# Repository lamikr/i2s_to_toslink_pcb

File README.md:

I2S to Toslink PCB

Kicad 7.0 schematic and PCB project for PCB that
can generate optical AES/EBU signal for Toslink audio adapter. PCB uses the
WM8805 chipset as a codec for transforming the signal from I2S to AES/EBU Toslink.

PCB has following input pins:
- 5V power
- GND
- I2S data
- I2S LRCLK
- I2S BCLK
- I2S MCLK (optional)

PCB can either be configured to use the external MCLK or generate the MCLK from the BCLK.
Generation of MCLK is usually needed because the WM8805 does not always work with the external
MCLK and that is hearable as a small errors and cracks on audio.

Project will also need the firmware for ATmega chip so that it can configure the PLL generator
and WM8805 over I2C lines to right mode.

By default the WM8805 codec GPO0 and GPO7 are pulled down so that the WM8805 is configured to use 16 bit I2S data.
But those gpio's can be pulled also to UP to 3V3 voltage to configure the WM8805 to handle 24 bit I2S data if needed.
(see wm8805 docs for details). Codec can also be resetted externally via reset pin. (ATmega has free gpios with headers to drive those pins if you want to add the jumper wires and modify firmware)

[Schematics in PDF document](./docs/schematics/schematics.pdf)

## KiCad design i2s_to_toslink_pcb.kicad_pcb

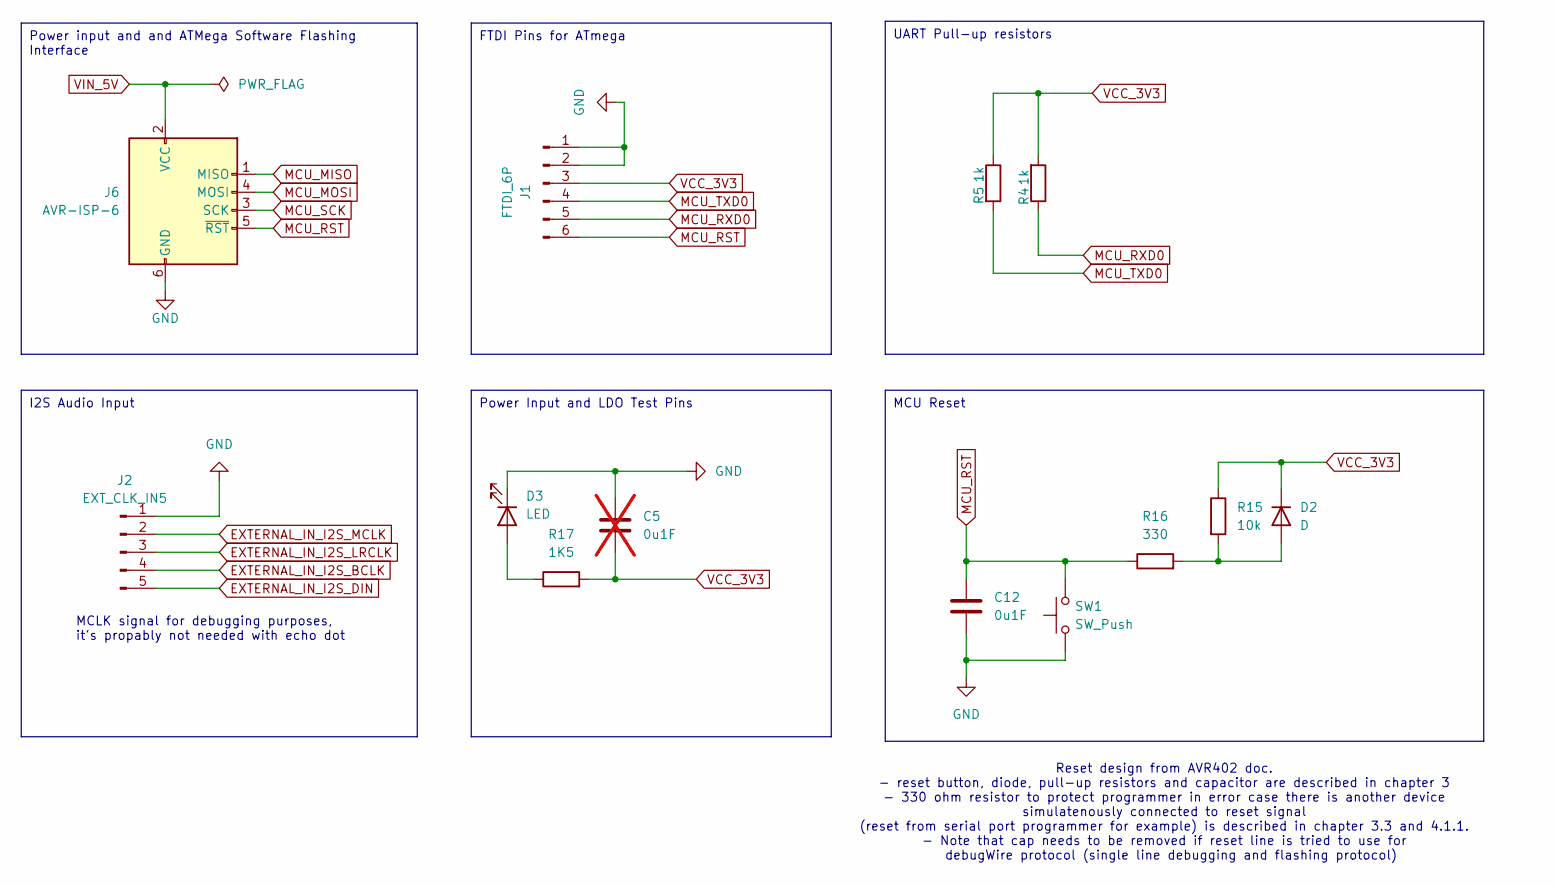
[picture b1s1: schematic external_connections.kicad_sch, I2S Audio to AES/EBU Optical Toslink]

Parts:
C5: 0u1F; C_0603_1608Metric; MPN GRM033R61A104ME15D; not fitted
C12: 0u1F; C_0603_1608Metric
D2: D; D_0603_1608Metric
D3: LED; LED_0805_2012Metric; MPN QBLP631-AG
J1: FTDI_6P; PinHeader_1x06_P2.54mm_Vertical; MPN 10129378-920001BLF-ND
J2: EXT_CLK_IN5; PinHeader_1x05_P2.54mm_Vertical
J6: AVR-ISP-6; PinHeader_2x03_P2.54mm_Vertical; MPN 75869-131LF
R4: 1k; R_0603_1608Metric; MPN RC0402FR-0710KL
R5: 1k; R_0603_1608Metric; MPN RC0402FR-070RL
R15: 10k; R_0603_1608Metric
R16: 330; R_0603_1608Metric
R17: 1K5; R_0603_1608Metric; MPN RC0402FR-071K5L
SW1: SW_Push; SW_SPST_B3U-1000P

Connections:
EXTERNAL_IN_I2S_BCLK: J2.4; also elsewhere on the board
EXTERNAL_IN_I2S_DIN: J2.5; also elsewhere on the board
EXTERNAL_IN_I2S_LRCLK: J2.3; also elsewhere on the board
EXTERNAL_IN_I2S_MCLK: J2.2; also elsewhere on the board
GND: C5.1, C12.2, D3.1 (K), J1.1, J1.2, J2.1, J6.6 (GND), SW1.1; also elsewhere on the board
MCU_MISO: J6.1 (MISO); also elsewhere on the board
MCU_MOSI: J6.4 (MOSI); also elsewhere on the board
MCU_RST: C12.1, J1.6, J6.5 (~RST), R16.1, SW1.2; also elsewhere on the board
MCU_RXD0: J1.5, R4.1; also elsewhere on the board
MCU_SCK: J6.3 (SCK); also elsewhere on the board
MCU_TXD0: J1.4, R5.2; also elsewhere on the board
unnamed: D2.2 (A), R15.2, R16.2
unnamed: D3.2 (A), R17.1
VCC_3V3: C5.2, D2.1 (K), J1.3, R4.2, R5.1, R15.1, R17.2; also elsewhere on the board
VIN_5V: J6.2 (VCC); also elsewhere on the board

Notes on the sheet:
Power input and and ATMega Software Flashing Interface
MCU Reset
UART Pull-up resistors
FTDI Pins for ATmega
I2S Audio Input
Power Input and LDO Test Pins
MCLK signal for debugging purposes, it's propably not needed with echo dot
Reset design from AVR402 doc. - reset button, diode, pull-up resistors and capacitor are described in chapter 3 - 330 ohm resistor to protect programmer in error case there is another device simulatenously connected to reset signal (reset from serial port programmer for example) is described in cha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

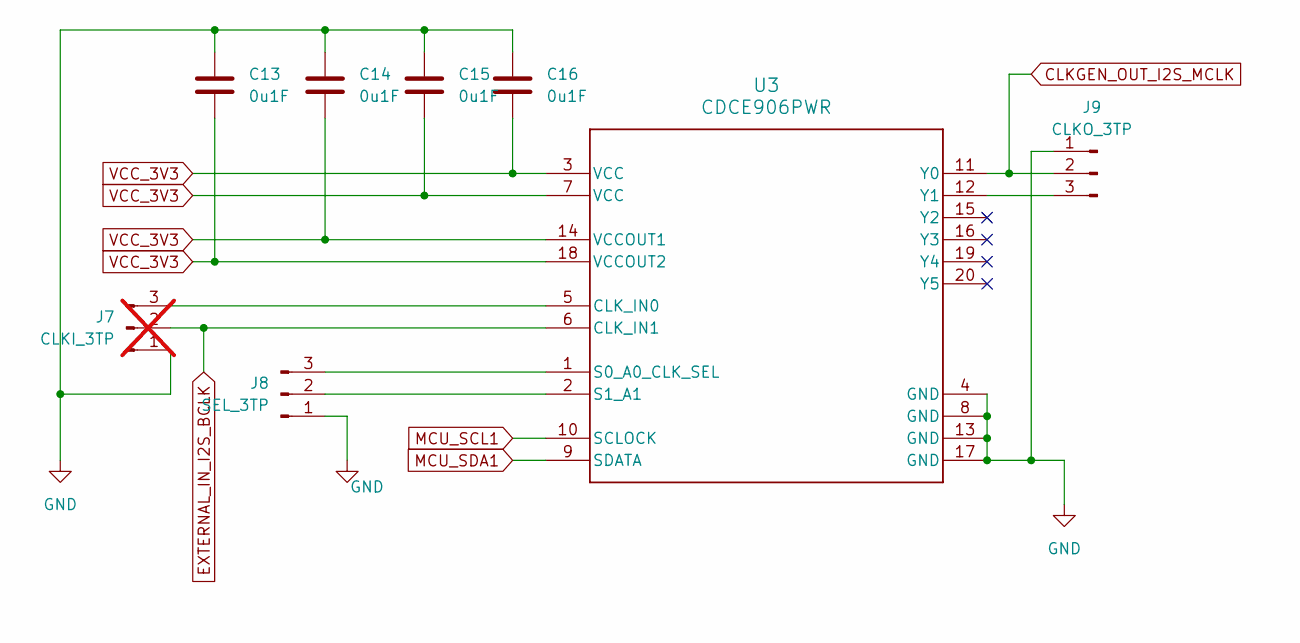
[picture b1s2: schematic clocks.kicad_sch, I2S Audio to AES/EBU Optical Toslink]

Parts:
C13, C14, C15, C16: 0u1F; C_0603_1608Metric; MPN GRM033R61A104ME15D
J7: CLKI_3TP; PinHeader_1x03_P2.54mm_Vertical; not fitted
J8: SEL_3TP; PinHeader_1x03_P2.54mm_Vertical
J9: CLKO_3TP; PinHeader_1x03_P2.54mm_Vertical
U3: CDCE906PWR; PW0020A-IPC_A; MPN CDCE906PWR

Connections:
CLKGEN_OUT_I2S_MCLK: J9.2, U3.11 (Y0); also elsewhere on the board
EXTERNAL_IN_I2S_BCLK: J7.2, U3.6 (CLK_IN1); also elsewhere on the board
GND: C13.1, C14.1, C15.1, C16.1, J7.1, J8.1, J9.1, U3.4 (GND), U3.8 (GND), U3.13 (GND), U3.17 (GND); also elsewhere on the board
MCU_SCL1: U3.10 (SCLOCK); also elsewhere on the board
MCU_SDA1: U3.9 (SDATA); also elsewhere on the board
unnamed: J7.3, U3.5 (CLK_IN0)
unnamed: J8.2, U3.2 (S1_A1)
unnamed: J8.3, U3.1 (S0_A0_CLK_SEL)
unnamed: J9.3, U3.12 (Y1)
VCC_3V3: C13.2, C14.2, C15.2, C16.2, U3.3 (VCC), U3.7 (VCC), U3.14 (VCCOUT1), U3.18 (VCCOUT2); also elsewhere on the board

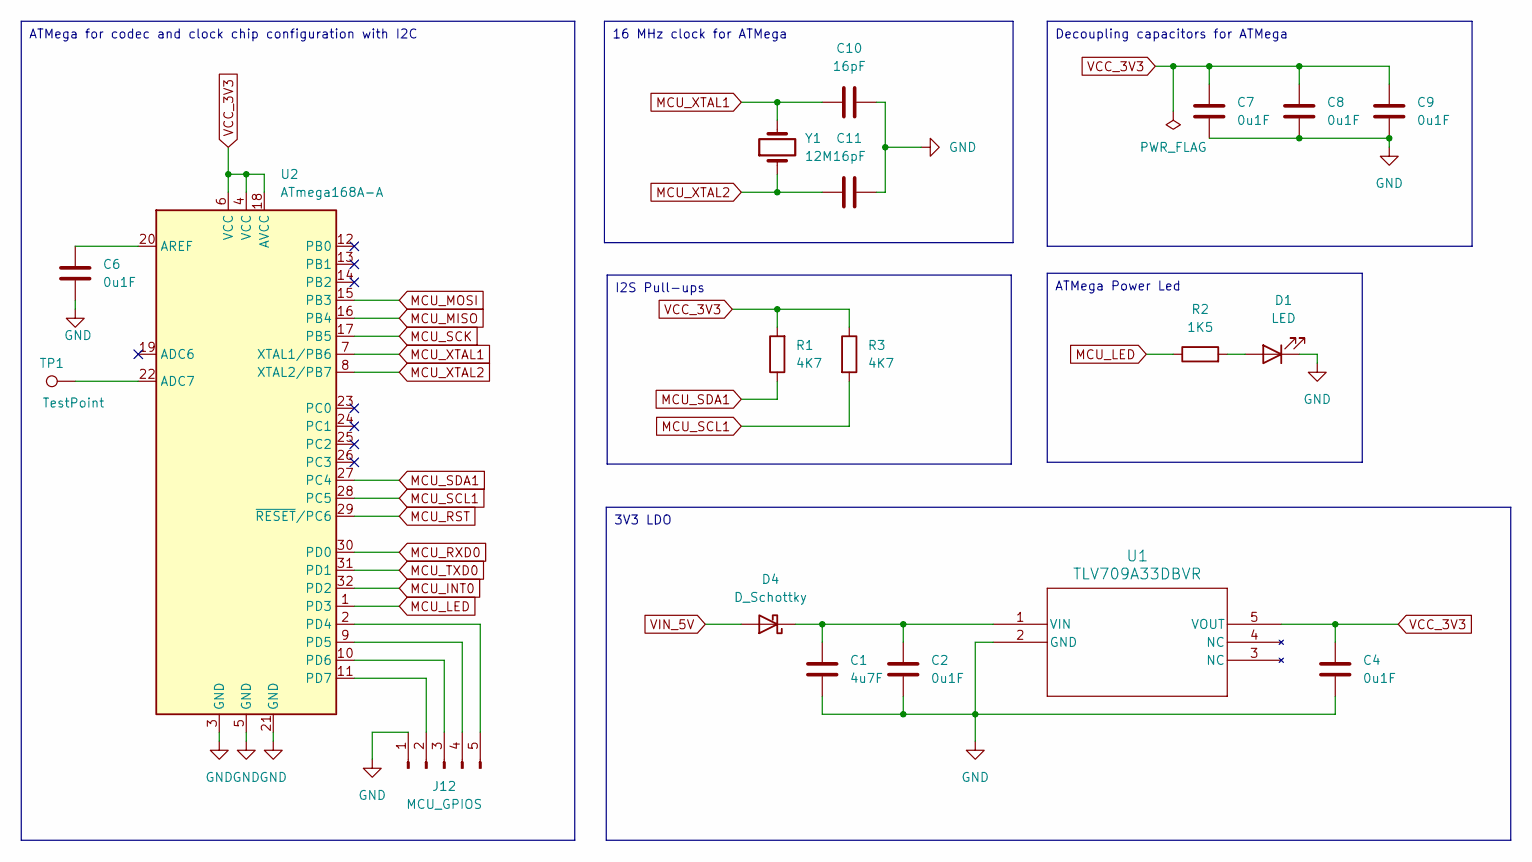
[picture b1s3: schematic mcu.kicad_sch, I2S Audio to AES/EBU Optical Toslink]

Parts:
C1: 4u7F; C_0603_1608Metric; MPN GRM155R60J475ME47D
C2, C4, C6, C7, C8, C9: 0u1F; C_0603_1608Metric; MPN GRM033R61A104ME15D
C10, C11: 16pF; C_0402_1005Metric; MPN GJM1555C1H160GB01D
D1: LED; LED_0805_2012Metric; MPN QBLP631-AG
D4: D_Schottky; D_0603_1608Metric
J12: MCU_GPIOS; PinHeader_1x05_P2.54mm_Vertical
R1, R3: 4K7; R_0603_1608Metric; MPN RC0402FR-074K7L
R2: 1K5; R_0603_1608Metric; MPN RC0402FR-071K5L
TP1: TestPoint; TestPoint_Pad_D1.0mm
U1: TLV709A33DBVR; SOT-23-5_DBV_TEX; MPN TLV709A33DBVR
U2: ATmega168A-A; TQFP-32_7x7mm_P0.8mm; MPN ATMEGA168A-AUR
Y1: 12M; XTAL_ABM7-12.000MHZ-D2Y-T; MPN ABM7-12.000MHZ-D2Y-T

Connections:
GND: C1.2, C2.2, C4.2, C6.2, C7.2, C8.2, C9.2, C10.2, C11.2, D1.1 (K), J12.1, U1.2 (GND), U2.3 (GND), U2.5 (GND), U2.21 (GND); also elsewhere on the board
MCU_INT0: U2.32 (PD2); also elsewhere on the board
MCU_LED: R2.1, U2.1 (PD3)
MCU_MISO: U2.16 (PB4); also elsewhere on the board
MCU_MOSI: U2.15 (PB3); also elsewhere on the board
MCU_RST: U2.29 (~RESET/PC6); also elsewhere on the board
MCU_RXD0: U2.30 (PD0); also elsewhere on the board
MCU_SCK: U2.17 (PB5); also elsewhere on the board
MCU_SCL1: R3.2, U2.28 (PC5); also elsewhere on the board
MCU_SDA1: R1.1, U2.27 (PC4); also elsewhere on the board
MCU_TXD0: U2.31 (PD1); also elsewhere on the board
MCU_XTAL1: C10.1, U2.7 (XTAL1/PB6), Y1.2
MCU_XTAL2: C11.1, U2.8 (XTAL2/PB7), Y1.1
unnamed: D1.2 (A), R2.2
unnamed: C1.1, C2.1, D4.1 (K), U1.1 (VIN)
unnamed: J12.2, U2.11 (PD7)
unnamed: J12.3, U2.10 (PD6)
unnamed: J12.4, U2.9 (PD5)
unnamed: J12.5, U2.2 (PD4)
unnamed: TP1.1, U2.22 (ADC7)
unnamed: C6.1, U2.20 (AREF)
VCC_3V3: C4.1, C7.1, C8.1, C9.1, R1.2, R3.1, U1.5 (VOUT), U2.4 (VCC), U2.6 (VCC), U2.18 (AVCC); also elsewhere on the board
VIN_5V: D4.2 (A); also elsewhere on the board

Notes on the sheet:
16 MHz clock for ATMega
ATMega for codec and clock chip configuration with I2C
ATMega Power Led
I2S Pull-ups
3V3 LDO
Decoupling capacitors for ATMega

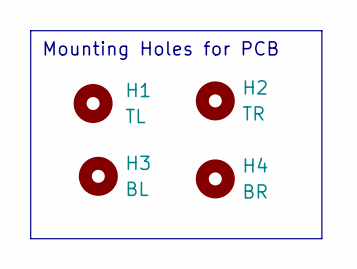
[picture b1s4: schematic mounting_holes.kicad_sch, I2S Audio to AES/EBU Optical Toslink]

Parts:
H1: TL; MountingHole_2.2mm_M2_ISO7380_Pad_TopBottom
H2: TR; MountingHole_2.2mm_M2_ISO7380_Pad_TopBottom
H3: BL; MountingHole_2.2mm_M2_ISO7380_Pad_TopBottom
H4: BR; MountingHole_2.2mm_M2_ISO7380_Pad_TopBottom

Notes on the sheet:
Mounting Holes for PCB

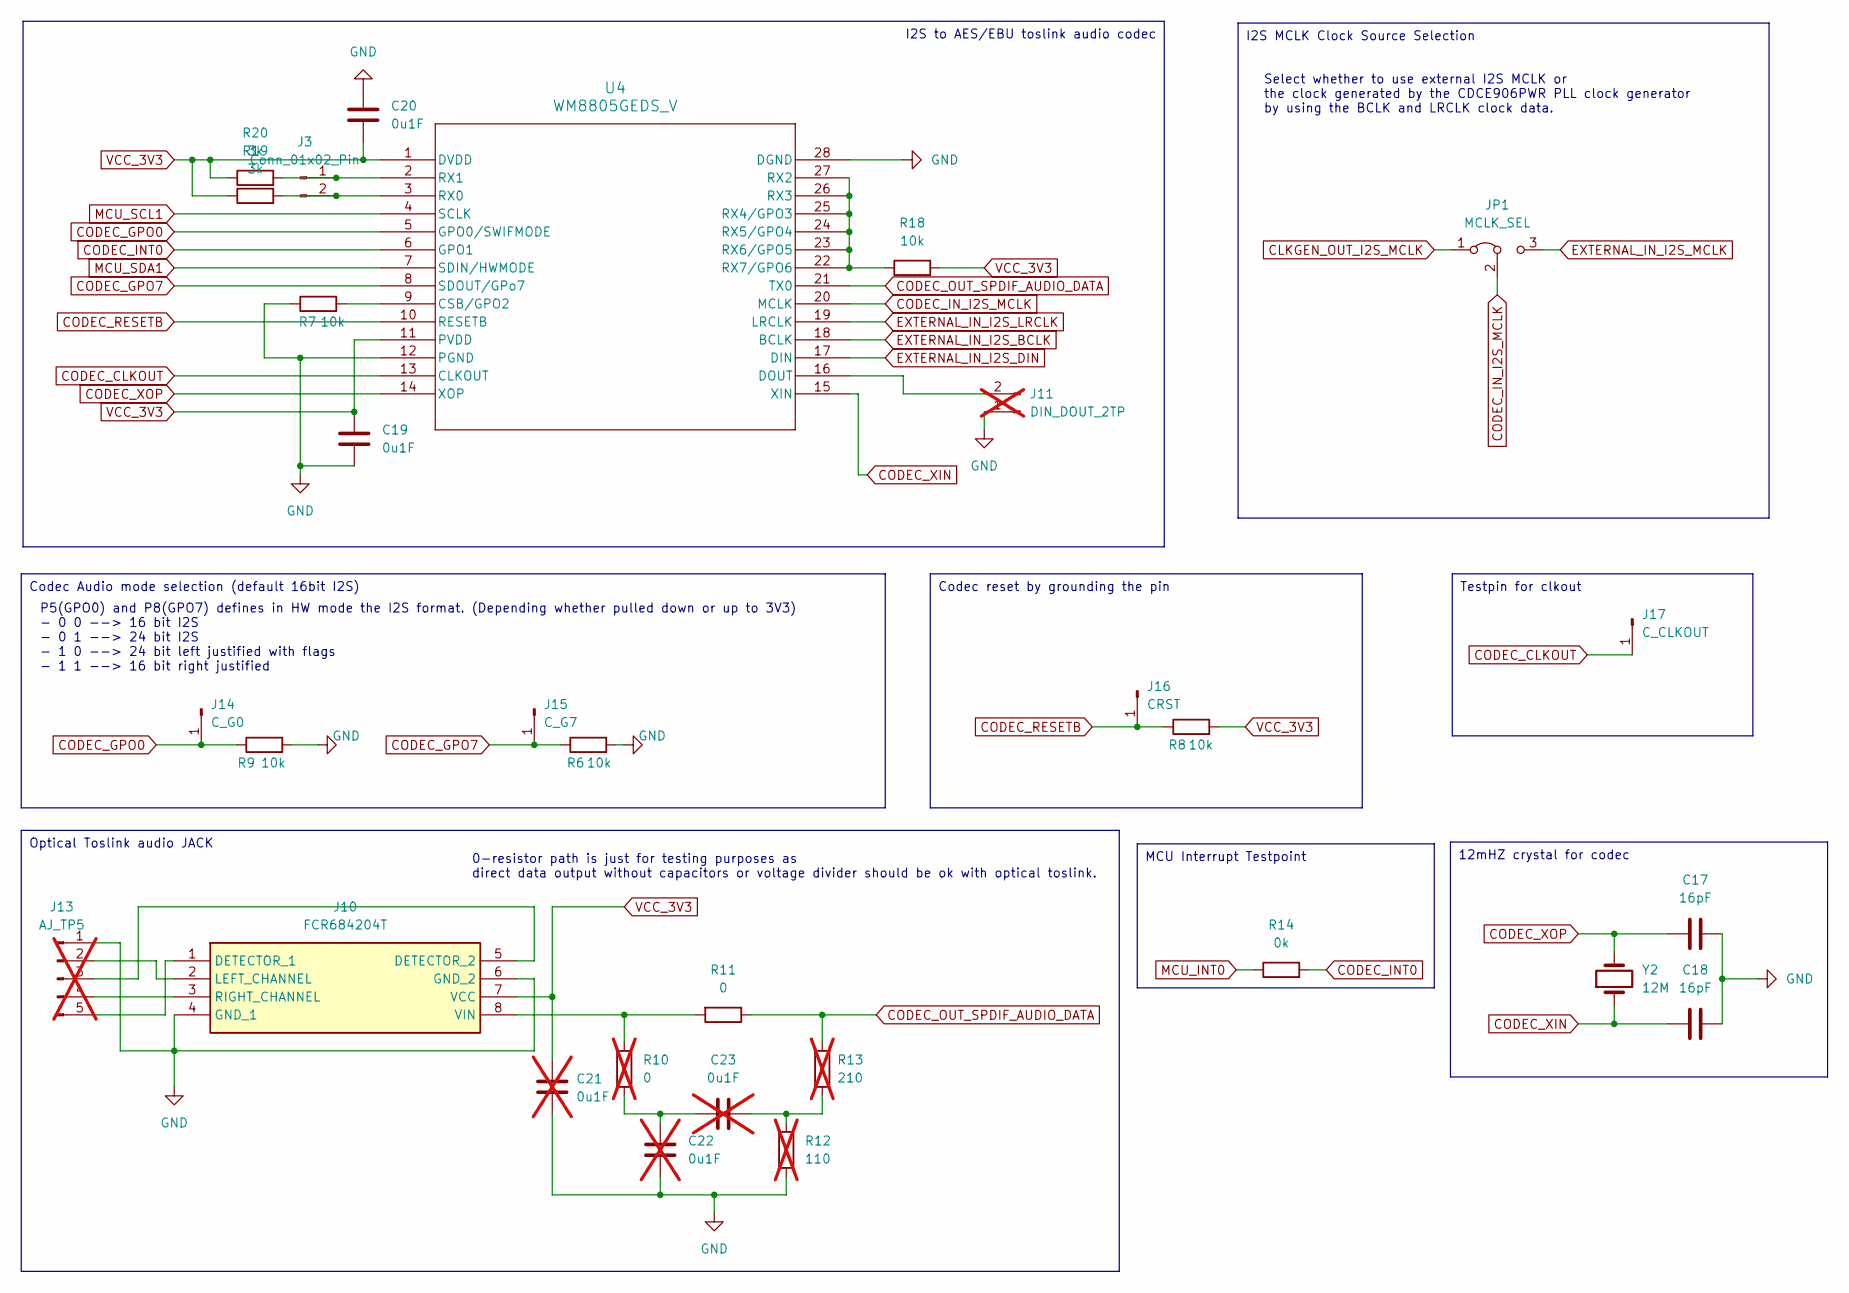
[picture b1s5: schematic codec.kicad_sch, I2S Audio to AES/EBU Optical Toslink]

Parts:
C17, C18: 16pF; C_0603_1608Metric; MPN GJM1555C1H160GB01D
C19, C20: 0u1F; C_0603_1608Metric; MPN GRM033R61A104ME15D
C21: 0u1F; C_0603_1608Metric; MPN GRM033R61A104ME15D; not fitted
C22, C23: 0u1F; C_0603_1608Metric; MPN GCJ188R71H104KA12D; not fitted
J3: Conn_01x02_Pin; PinHeader_1x02_P2.54mm_Vertical
J10: FCR684204T; MPN FCR684204T
J11: DIN_DOUT_2TP; PinHeader_1x02_P2.00mm_Vertical; MPN HPH1-A-20-UA; not fitted
J13: AJ_TP5; PinHeader_1x05_P2.00mm_Vertical; MPN S9014E-05-ND; not fitted
J14: C_G0; PinHeader_1x01_P1.27mm_Vertical
J15: C_G7; PinHeader_1x01_P1.27mm_Vertical
J16: CRST; PinHeader_1x01_P1.27mm_Vertical
J17: C_CLKOUT; PinHeader_1x01_P1.27mm_Vertical
JP1: MCLK_SEL; PinHeader_1x03_P2.54mm_Vertical
R6, R7, R8, R9: 10k; R_0603_1608Metric; MPN RC0402FR-0710KL
R10: 0; R_0603_1608Metric; MPN RC0603JR-070RL; not fitted
R11: 0; R_0603_1608Metric; MPN RC0603JR-070RL
R12: 110; R_0603_1608Metric; MPN RC0603JR-07110RL; not fitted
R13: 210; R_0603_1608Metric; MPN RC0603FR-07210RL; not fitted
R14: 0k; R_0603_1608Metric
R18: 10k; R_0603_1608Metric
R19, R20: 3k; R_0603_1608Metric
U4: WM8805GEDS_V; SSOP28_WM8805GEDS_V_CIR; MPN WM8805GEDS_V
Y2: 12M; XTAL_ABM7-12.000MHZ-D2Y-T; MPN ABM7-12.000MHZ-D2Y-T

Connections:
CLKGEN_OUT_I2S_MCLK: JP1.1 (A); also elsewhere on the board
CODEC_CLKOUT: J17.1, U4.13 (CLKOUT)
CODEC_GPO0: J14.1, R9.1, U4.5 (GPO0/SWIFMODE)
CODEC_GPO7: J15.1, R6.1, U4.8 (SDOUT/GPo7)
CODEC_INT0: R14.2, U4.6 (GPO1)
CODEC_IN_I2S_MCLK: JP1.2 (C), U4.20 (MCLK)
CODEC_OUT_SPDIF_AUDIO_DATA: R11.1, R13.2, U4.21 (TX0)
CODEC_RESETB: J16.1, R8.1, U4.10 (RESETB)
CODEC_XIN: C18.1, U4.15 (XIN), Y2.1
CODEC_XOP: C17.1, U4.14 (XOP), Y2.2
EXTERNAL_IN_I2S_BCLK: U4.18 (BCLK); also elsewhere on the board
EXTERNAL_IN_I2S_DIN: U4.17 (DIN); also elsewhere on the board
EXTERNAL_IN_I2S_LRCLK: U4.19 (LRCLK); also elsewhere on the board
EXTERNAL_IN_I2S_MCLK: JP1.3 (B); also elsewhere on the board
GND: C17.2, C18.2, C19.2, C20.1, C21.2, C22.2, J10.4 (GND_1), J10.6 (GND_2), J11.1, J13.1, R6.2, R7.1, R9.2, R12.2, U4.12 (PGND), U4.28 (DGND); also elsewhere on the board
MCU_INT0: R14.1; also elsewhere on the board
MCU_SCL1: U4.4 (SCLK); also elsewhere on the board
MCU_SDA1: U4.7 (SDIN/HWMODE); also elsewhere on the board
unnamed: C22.1, C23.1, R10.2
unnamed: C23.2, R12.1, R13.1
unnamed: J3.1, R20.2, U4.2 (RX1)
unnamed: J3.2, R19.2, U4.3 (RX0)
unnamed: J10.1 (DETECTOR_1), J13.5
unnamed: J10.5 (DETECTOR_2), J13.3
unnamed: J10.2 (LEFT_CHANNEL), J13.2
unnamed: J10.3 (RIGHT_CHANNEL), J13.4
unnamed: J10.8 (VIN), R10.1, R11.2
unnamed: J11.2, U4.16 (DOUT)
unnamed: R7.2, U4.9 (CSB/GPO2)
unnamed: R18.1, U4.22 (RX7/GPO6), U4.23 (RX6/GPO5), U4.24 (RX5/GPO4), U4.25 (RX4/GPO3), U4.26 (RX3), U4.27 (RX2)
VCC_3V3: C19.1, C20.2, C21.1, J10.7 (VCC), R8.2, R18.2, R19.1, R20.1, U4.1 (DVDD), U4.11 (PVDD); also elsewhere on the board

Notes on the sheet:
MCU Interrupt Testpoint
Optical Toslink audio JACK
12mHZ crystal for codec
Codec Audio mode selection (default 16bit I2S)
Codec reset by grounding the pin
Testpin for clkout
I2S to AES/EBU toslink audio codec
I2S MCLK Clock Source Selection
Select whether to use external I2S MCLK or the clock generated by the CDCE906PWR PLL clock generator by using the BCLK and LRCLK clock data.
P5(GPO0) and P8(GPO7) defines in HW mode the I2S format. (Depending whether pulled down or up to 3V3) - 0 0 --> 16 bit I2S - 0 1 --> 24 bit I2S - 1 0 --> 24 bit left justified with flags - 1 1 --> 16 bit right justified
0-resistor path is just for testing purposes as direct data output without capacitors or voltage divider should be ok with optical toslink.

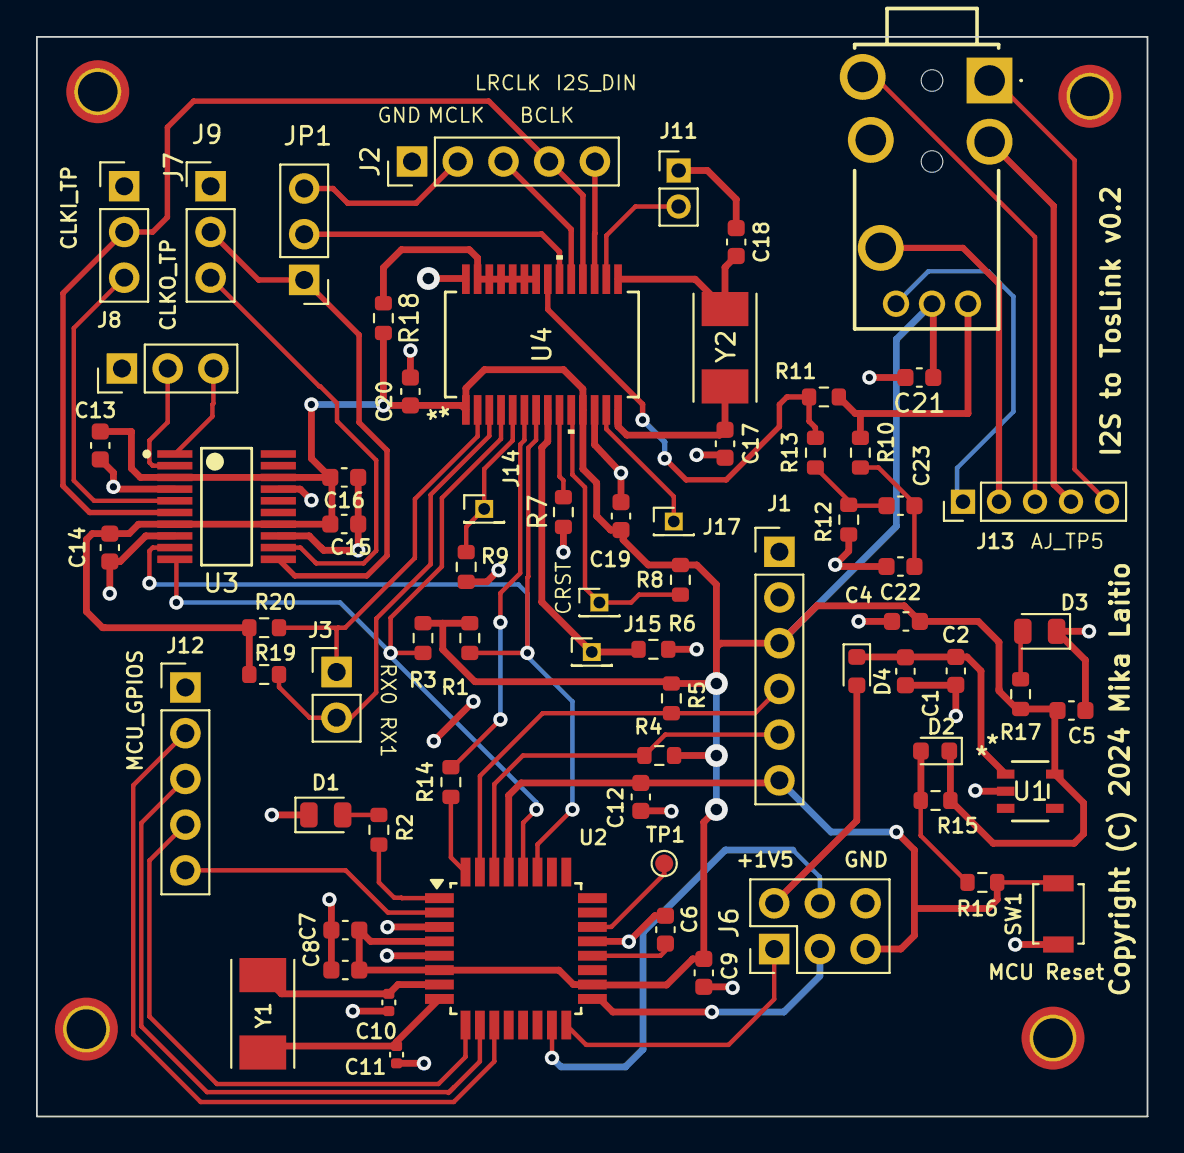
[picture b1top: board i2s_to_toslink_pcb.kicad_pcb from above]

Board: 2 copper layers, 61.7 x 60.0 mm, 74 parts (0 on the bottom side), 55 nets.

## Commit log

2023-12-26 initial schematics and pcb ready
2023-12-26 added version information
2023-12-26 small text description for LDO
2023-12-26 move external docs to own folder
2023-12-26 printed pdf from schematics
2023-12-26 exported gerber and 3d pcb files
2023-12-26 updated gitignore
2023-12-26 add link to pic and pdf
2023-12-26 small doc update
2023-12-26 small layout changes for some components
2023-12-27 added mpn and sku_digikey numbers for bom
2023-12-27 added led that was missing from bom
2023-12-27 bomlink csv update
2023-12-27 change gerber file location
2023-12-27 optimized bom from digikey
2024-01-18 cleaned up some vias not required
2024-01-18 added version label v0.1 to pcb
2024-02-08 10 percentage solder mask clearance
    - reduced the size of solder mask for
    CDCE906PWR, WM8805GEDS_V and ATMega168
    about 10 percentage. This will reduce the
    size of holes on pins very close to each others
    and thus help to spread the soldermask in a way
    that pins with soldermask will not touch
2024-03-18 doc rename
2024-03-18 ibom plugin files
2024-03-18 updated the symbol pin types
2024-03-18 various updates
    - removed duplicates 5V power connectors
    - now the whole pcb is always powered via 6 pin
    atmega avr isp connector
    - added connector for wm8805 rx0 and rx1
    - added labels for jumpers/connectors
    - moved the orientation of existing connecors
2024-03-19 finished v0.2 design
    - mcu ftdi serial connector reset pin
    to 3v3 instead of 5v
    - 3.3v pull-up resistor, cap and diode for mcu reset
    - mcu reset button
    - solder paste clearance -20% for
    mcu, codec, clk gen and ldo to help
2024-03-19 inceased the size of some tp headers to 2.00mm
2024-03-21 abm7 crystal and atmega1608 datasheets
2024-03-21 component footprint updates
    - 0402 caps and resistors to 0603
    - reset pin-header to reset button
2024-03-21 16M mcu crystal changed to 12M
    - Atmel168A crystal max frequency can be about
    13.3 Mhz for 3V3 voltage.
    See atmega168a datasheet Figure 29-1. Maximum Frequency vs. VCC
    --> 10MHz + 10Mhz/(4.5 - 2.7) * (3.3 - 2.7) = 13.3Mhz
2024-03-23 updated the kicad generated docs
    - schematics and 3d view of pcb
2024-03-24 add pull-up resistors for codex rx-pins
    - add connectors for rx0 and rx1 pins
    - rest of the rx-pins not reserved for use
    and they will share a common pull-up.
2024-04-03 added avr design notes doc
2024-04-03 rework the atmega168 reset signal schematics and routing
2024-04-03 updated gerber and bom files
2024-04-11 esp32-c6-wroom-1 symbol and footprint
2024-04-11 esp32-s3 and esp32-c6-wroom-1 specs
2024-04-11 some notes related to relation between i2s clocks
2024-04-11 added atmega168a firmware
    - firmware for v0.1 pcb version
    (with some after ward reset line hw fixes...)
    - firmware can communicate and configure both the wm8805 and
    cdce906 chipsets over i2s.
2024-04-12 cleaned routing on C7 and C8 area
2024-04-12 routing cleanups
2024-04-19 fix toslink pin6 grounding
    - had problem already on v1 boards
    - move toslink/3.5mm plug little out of board
    - re-arrange alternative output

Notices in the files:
i2s_to_toslink_pcb.kicad_pcb:
Copyright (C) 2024 Mika Laitio
